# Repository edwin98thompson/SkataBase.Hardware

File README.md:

# SkataBase – Hardware

Hardware development repository for **SkataBase**, a skateboard motion tracking and analytics platform.

This repository contains the electronic hardware design files, PCB layouts, component libraries and manufacturing documentation for the SkataBase SkateIMU device.

The device is designed to capture skateboard motion and orientation data using an onboard IMU, enabling trick detection, session tracking and performance analysis.

## Project Overview

SkateIMU is a compact, skateboard-mounted motion tracking device built around an ESP32 microcontroller and a 9-axis inertial measurement unit (IMU).

The hardware is being developed to provide reliable motion data acquisition during skateboarding, with particular emphasis on detecting and analysing individual skateboard tricks.

### Key Features

- 9-axis motion sensing (accelerometer, gyroscope and magnetometer).
- ESP32-C6-based embedded processing.
- SPI communication with the IMU.
- Bluetooth Low Energy (BLE) data transmission.
- Rechargeable LiPo battery operation.
- Compact PCB and enclosure designed for skateboard mounting.
- Modular hardware architecture to support future revisions.

## Hardware Architecture

| Component | Description |
|---|---|
| Microcontroller | Seeed Studio XIAO ESP32-C6 |
| IMU | ICM-20948 9-axis sensor |
| IMU Interface | SPI |
| Wireless Communication | Bluetooth Low Energy |
| Power Source | Rechargeable LiPo battery |
| Battery Capacity | 350 mAh (prototype target) |
| PCB Design | KiCad |

### System Architecture

The XIAO ESP32-C6 handles IMU data acquisition, sensor fusion and BLE communication.

The ICM-20948 provides accelerometer, gyroscope and magnetometer measurements. These measurements are processed by the firmware and transmitted to the Android application for visualisation and analysis.

## Development Status

**Current stage: PCB development and prototyping**

The initial proof of concept has successfully demonstrated:

- Real-time IMU data acquisition.
- SPI communication between the ESP32-C6 and ICM-20948.
- Madgwick sensor fusion for orientation estimation.
- BLE data transmission to the Android application.
- Successful preliminary skateboard testing.
- Reliable operation during skateboard impacts.

The project is now progressing towards a custom PCB and mechanically integrated enclosure.

### Upcoming Development

- [ ] Finalise schematic and component selection.
- [ ] Complete PCB layout and design rule checks.
- [ ] Validate power management and battery monitoring.
- [ ] Prototype momentary-button power control and deep-sleep operation.
- [ ] Manufacture initial PCB revision.
- [ ] Validate SPI sampling and BLE operation on the custom PCB.
- [ ] Design and manufacture 3D-printed enclosure.
- [ ] Perform extended skateboard field testing.

## Design Tools

| Tool | Purpose |
|---|---|
| KiCad | Schematic capture and PCB design |
| PlatformIO | Firmware development |
| Git | Version control |
| 3D CAD | Mechanical enclosure development |

## Manufacturing

Manufacturing files will be maintained alongside the relevant hardware revision.

Expected outputs include:

- Gerber files.
- NC drill files.
- Bill of Materials (BOM).
- Component placement / Pick and Place files.
- Assembly documentation.

Manufacturing outputs should be associated with a specific hardware revision to maintain traceability.

## Hardware Revisions

Hardware revisions will be tracked independently of firmware and Android application versions.

| Revision | Description | Status |
|---|---|---|
| Prototype 0 | Breadboard and breakout-board proof of concept | Completed |
| PCB Rev 1 | Initial custom PCB integrating ESP32-C6 and IMU | In development |

## Related Repositories

SkataBase is organised into separate repositories to keep hardware, firmware and application development independent.

- **Hardware:** This repository – KiCad designs and manufacturing files.
- **Firmware:** ESP32 firmware, sensor fusion and BLE implementation.
- **Android:** Android application for device configuration, data collection and analysis.
- **Project Hub:** Overall project documentation and links to all repositories.

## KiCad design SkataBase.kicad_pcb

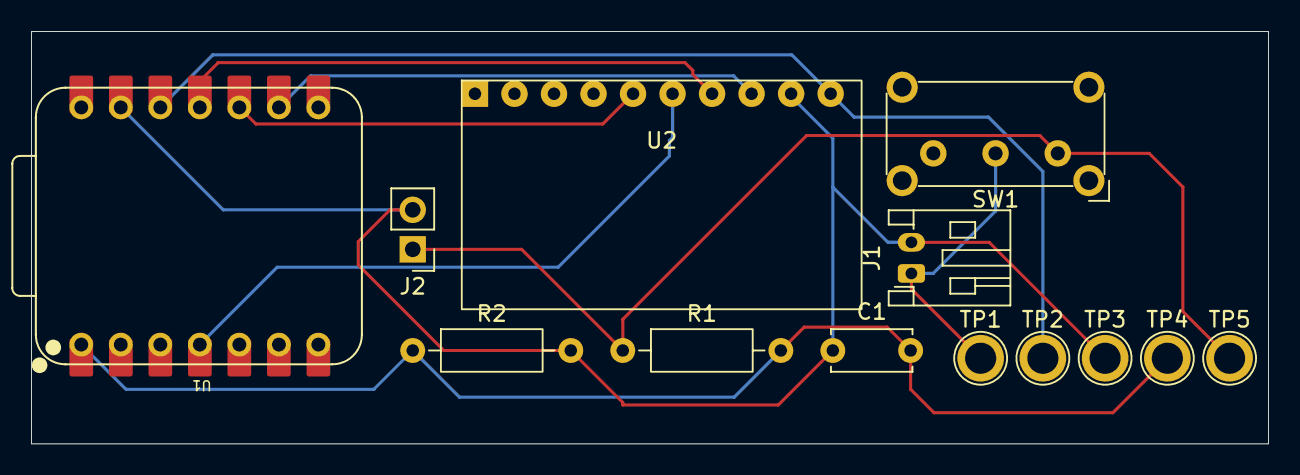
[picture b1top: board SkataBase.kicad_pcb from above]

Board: 2 copper layers, 79.5 x 26.5 mm, 13 parts (0 on the bottom side), 9 nets.

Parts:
C1: 100 nF; C_Disc_D5.0mm_W2.5mm_P5.00mm
J1: Conn_01x02; JST_PH_S2B-PH-K_1x02_P2.00mm_Horizontal
J2: Conn_01x02_Pin; PinHeader_1x02_P2.54mm_Vertical
R1, R2: 100K; R_Axial_DIN0207_L6.3mm_D2.5mm_P10.16mm_Horizontal
SW1: SW_SPDT; SW_E-Switch_EG1224_SPDT_Angled
TP1, TP2, TP3, TP4, TP5: TestPoint; TestPoint_Plated_Hole_D2.0mm
U1: XIAO-Add-On; XIAO-ESP32-C6-DIP
U2: ECP20948_Breakout; ECP20948_Breakout_26x15mm

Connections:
/3V3: TP2.1 (1_1), U1.12 (3V3_OUT), U2.10 (VCC)
/BATTERY_SENSE: C1.2, R1.2, R2.1, TP4.1 (1_1), U1.1 (D0)
/GND: C1.1, J1.2, J2.2, R2.2, TP3.1 (1_1), U1.13 (GND), U2.9 (GND)
/IMU_CS: U1.4 (D3), U2.6 (NCS)
/IMU_MISO: U1.10 (D9), U2.5 (ADO)
/IMU_MOSI: U1.11 (D10), U2.7 (SDA)
/IMU_SCK: U1.9 (D8), U2.8 (SCL)
/VBAT: J1.1, SW1.2 (B), TP1.1 (1_1)
/VBAT_SWITCHED: J2.1, R1.1, SW1.1 (A), TP5.1 (1_1)
